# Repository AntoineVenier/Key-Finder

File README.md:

# Key Tracker

The goal of this project is to design a small embedded device that you can attach to your key in order to find them when they are lost.

## How it work

On the board which is attach to your key you have nucleo board which communicate with a GPS and Send the Location of the key to a mobile application thanks to a Bluetooth Module.
You can also detect the location of the key by making sound the buzzer.

                                    TOP

                                     BOTTOM

            Application Welcome page

            Application choice page

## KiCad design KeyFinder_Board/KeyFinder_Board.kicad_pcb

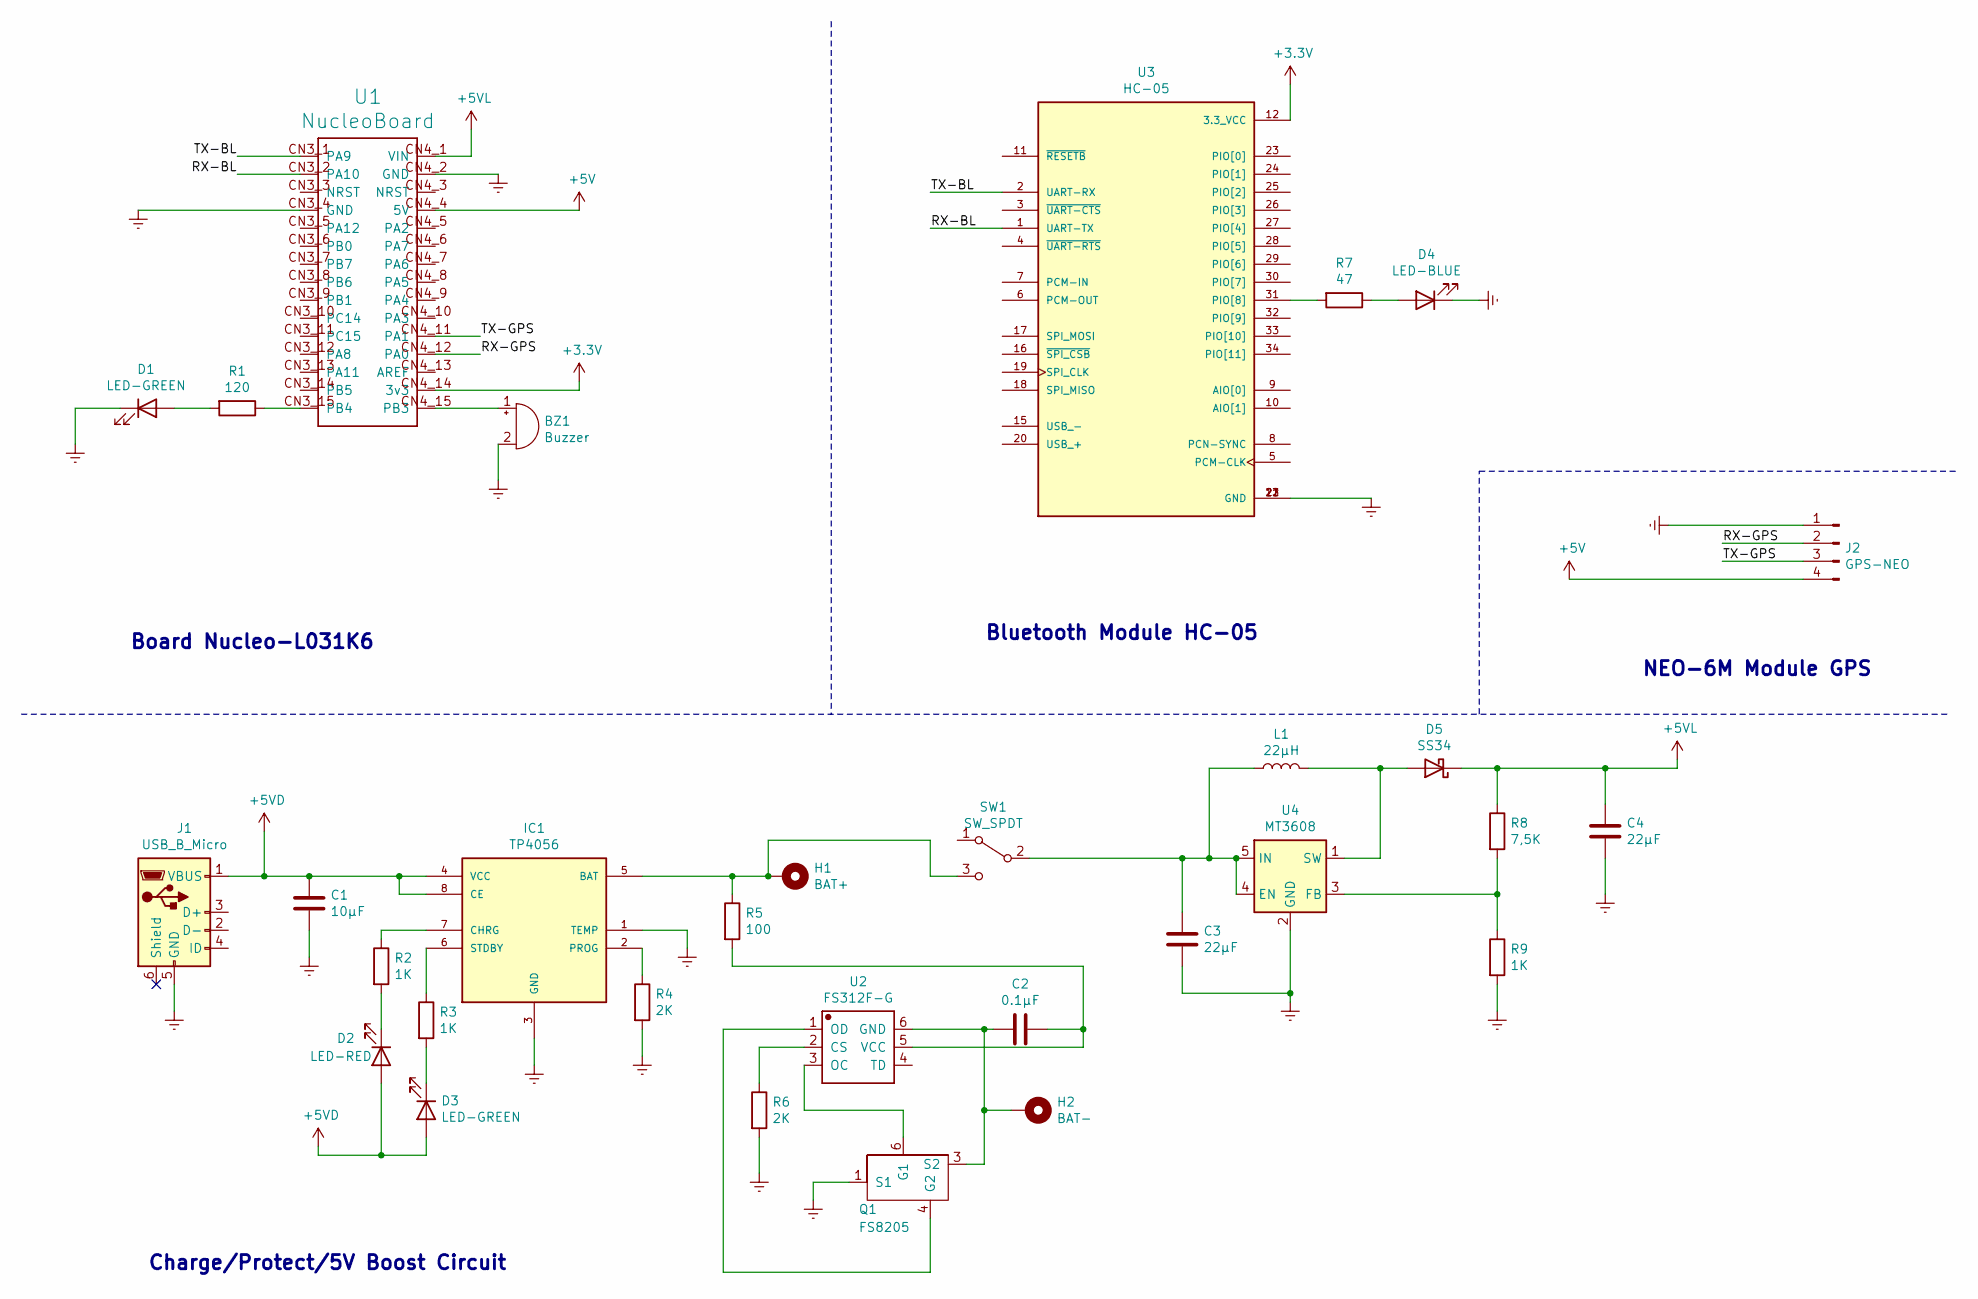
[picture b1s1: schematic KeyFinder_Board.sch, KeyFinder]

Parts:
BZ1: Buzzer; Buzzer_12x9.5RM7.6
C1: 10µF; C_0603_1608Metric_Pad1.08x0.95mm_HandSolder; LCSC C19702
C2: 0.1µF; C_0603_1608Metric_Pad1.08x0.95mm_HandSolder; LCSC C14663
C3, C4: 22µF; C_1812_4532Metric_Pad1.57x3.40mm_HandSolder; LCSC C59461
D1, D3: LED-GREEN; LED_0603_1608Metric_Pad1.05x0.95mm_HandSolder; LCSC C72043
D2: LED-RED; LED_0603_1608Metric_Pad1.05x0.95mm_HandSolder; LCSC C2286
D4: LED-BLUE; LED_0603_1608Metric_Pad1.05x0.95mm_HandSolder; LCSC C72041
D5: SS34; D_SMA; LCSC C8678
H1: BAT+; PinSocket_1x01_P2.54mm_Vertical
H2: BAT-; PinHeader_1x01_P2.54mm_Vertical
IC1: TP4056; SOP-8; LCSC C16581
J1: USB_B_Micro; USB_Micro-B_Molex_47346-0001; LCSC C404969
J2: GPS-NEO; PinHeader_1x04_P2.54mm_Vertical_SMD_Pin1Left
L1: 22µH; L_7.3x7.3_H4.5; LCSC C207843
Q1: FS8205; SOT-23-6_Handsoldering; LCSC C32254
R1: 120; R_0603_1608Metric_Pad0.98x0.95mm_HandSolder; LCSC C22787
R2, R3, R9: 1K; R_0603_1608Metric_Pad0.98x0.95mm_HandSolder; LCSC C21190
R4, R6: 2K; R_0603_1608Metric_Pad0.98x0.95mm_HandSolder; LCSC C22975
R5: 100; R_0603_1608Metric_Pad0.98x0.95mm_HandSolder; LCSC C22775
R7: 47; R_0603_1608Metric_Pad0.98x0.95mm_HandSolder; LCSC C23182
R8: 7,5K; R_0603_1608Metric_Pad0.98x0.95mm_HandSolder; LCSC C23234
SW1: SW_SPDT; SW_SPDT_CK-JS102011SAQN; LCSC C405951
U1: NucleoBoard; MODULE_NUCLEO-L432KC
U2: FS312F-G; SOT-23-6_Handsoldering; LCSC C82736
U3: HC-05; XCVR_HC-05; PARTREV v1.0
U4: MT3608; SOT-23-6; LCSC C84817

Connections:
+3V3: U1.CN4_14 (3v3), U3.12 (3.3_VCC)
+5V: J2.4, U1.CN4_4 (5V)
+5VD: C1.1, D2.2 (A), D3.2 (A), IC1.4 (VCC), IC1.8 (CE), J1.1 (VBUS)
+5VL: C4.1, D5.1 (K), R8.1, U1.CN4_1 (VIN)
/RX-BL: U1.CN3_2 (PA10), U3.1 (UART-TX)
/RX-GPS: J2.2, U1.CN4_12 (PA0)
/TX-BL: U1.CN3_1 (PA9), U3.2 (UART-RX)
/TX-GPS: J2.3, U1.CN4_11 (PA1)
GNDREF: BZ1.2 (+), C1.2, C3.2, C4.2, D1.1 (K), D4.1 (K), IC1.1 (TEMP), IC1.3 (GND), J1.5 (GND), J2.1, Q1.1 (S1), R4.2, R6.2, R9.2, U1.CN3_4 (GND), U1.CN4_2 (GND), U3.13 (GND), U3.21 (GND), U3.22 (GND), U4.2 (GND)
unnamed: BZ1.1 (-), U1.CN4_15 (PB3)
unnamed: C2.1, R5.2, U2.5 (VCC)
unnamed: C2.2, H2.1, Q1.3 (S2), U2.6 (GND)
unnamed: C3.1, L1.1, SW1.2 (B), U4.4 (EN), U4.5 (IN)
unnamed: D1.2 (A), R1.2
unnamed: D2.1 (K), R2.2
unnamed: D3.1 (K), R3.2
unnamed: D4.2 (A), R7.1
unnamed: D5.2 (A), L1.2, U4.1 (SW)
unnamed: H1.1, IC1.5 (BAT), R5.1, SW1.3 (C)
unnamed: IC1.2 (PROG), R4.1
unnamed: IC1.6 (STDBY), R3.1
unnamed: IC1.7 (CHRG), R2.1
unnamed: Q1.4 (G2), U2.1 (OD)
unnamed: Q1.6 (G1), U2.3 (OC)
unnamed: R1.1, U1.CN3_15 (PB4)
unnamed: R6.1, U2.2 (CS)
unnamed: R7.2, U3.31 (PIO[8])
unnamed: R8.2, R9.1, U4.3 (FB)

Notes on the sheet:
Charge/Protect/5V Boost Circuit
NEO-6M Module GPS
Board Nucleo-L031K6
Bluetooth Module HC-05

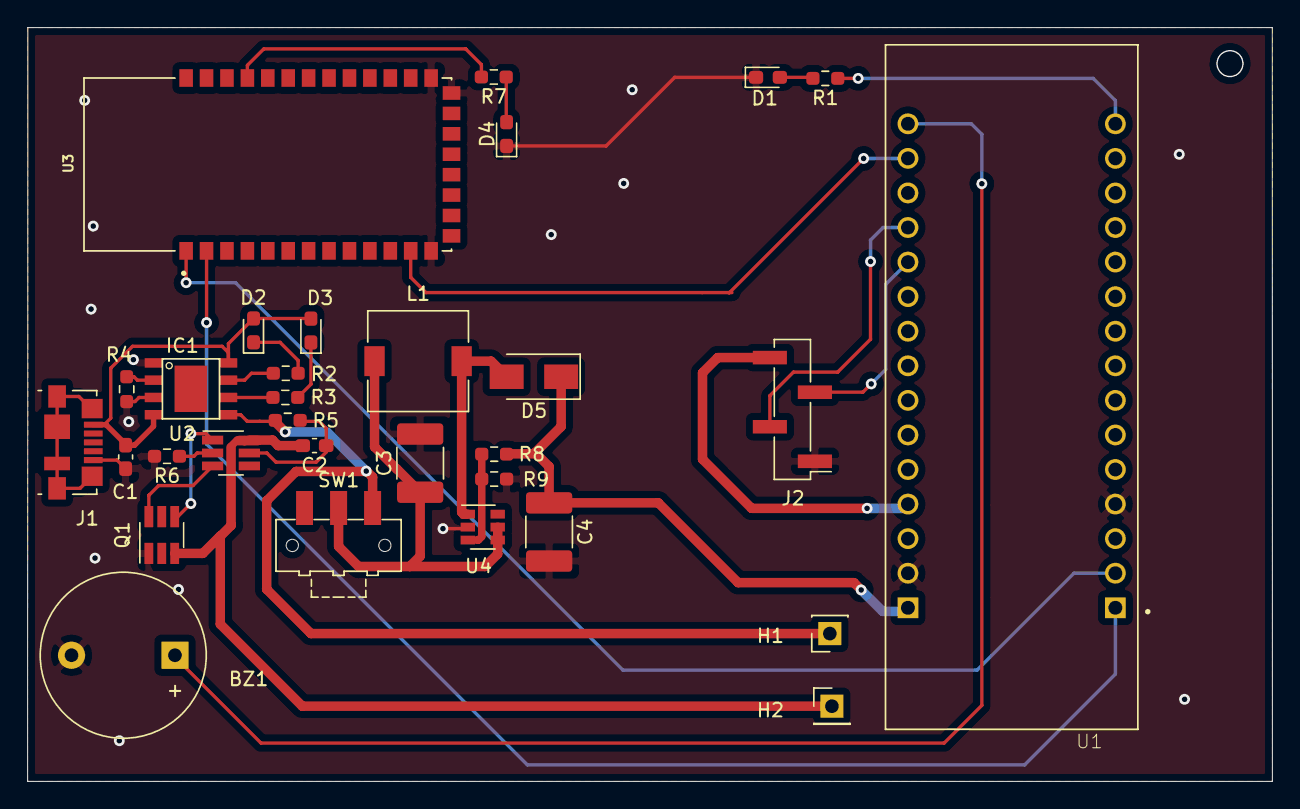
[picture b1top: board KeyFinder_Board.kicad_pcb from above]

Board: 2 copper layers, 91.5 x 55.4 mm, 31 parts (0 on the bottom side), 28 nets.

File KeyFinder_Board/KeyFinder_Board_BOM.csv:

Comment,Designator,Footprint,LCSC Part Numbers
10µF,C1,Capacitor_SMD:C_0603_1608Metric_Pad1.08x0.95mm_HandSolder,C19702
0.1µF,C2,Capacitor_SMD:C_0603_1608Metric_Pad1.08x0.95mm_HandSolder, C14663
22µF,"C3,C4",Capacitor_SMD:C_1812_4532Metric_Pad1.57x3.40mm_HandSolder,C59461
LED-RED,D2,LED_SMD:LED_0603_1608Metric_Pad1.05x0.95mm_HandSolder,C2286
LED-GREEN,"D1,D3",LED_SMD:LED_0603_1608Metric_Pad1.05x0.95mm_HandSolder, C72043
LED-BLUE,D4,LED_SMD:LED_0603_1608Metric_Pad1.05x0.95mm_HandSolder, C72041
SS34 ,D5,Diode_SMD:D_SMA,C8678
TP4056,IC1,mes_empreintes:SOP-8, C16581
USB_B_Micro,J1,Connector_USB:USB_Micro-B_Molex_47346-0001, C404969
22µH,L1,Inductor_SMD:L_7.3x7.3_H4.5, C237916
FS8205,Q1,mes_empreintes:FS312F-G_SOT-23-6, C32254
120,R1,Resistor_SMD:R_0603_1608Metric_Pad0.98x0.95mm_HandSolder,C22787
1K,"R2,R3,R9",Resistor_SMD:R_0603_1608Metric_Pad0.98x0.95mm_HandSolder,C21190
2K,"R4,R6",Resistor_SMD:R_0603_1608Metric_Pad0.98x0.95mm_HandSolder, C22975
100,R5,Resistor_SMD:R_0603_1608Metric_Pad0.98x0.95mm_HandSolder, C22775
47,R7,Resistor_SMD:R_0603_1608Metric_Pad0.98x0.95mm_HandSolder, C23182
"7,5K",R8,Resistor_SMD:R_0603_1608Metric_Pad0.98x0.95mm_HandSolder,C23234
SW_SPDT,SW1,Button_Switch_SMD:SW_SPDT_CK-JS102011SAQN, C405951
FS312F-G,U2,mes_empreintes:FS312F-G_SOT-23-6, C82736
MT3608,U4,Package_TO_SOT_SMD:SOT-23-6, C84817

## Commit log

2021-03-03 add Electronic folder
2021-03-03 add mobile application folder
2021-03-04 add README file
2021-03-04 add readmeimage
2021-03-04 add image to README file
